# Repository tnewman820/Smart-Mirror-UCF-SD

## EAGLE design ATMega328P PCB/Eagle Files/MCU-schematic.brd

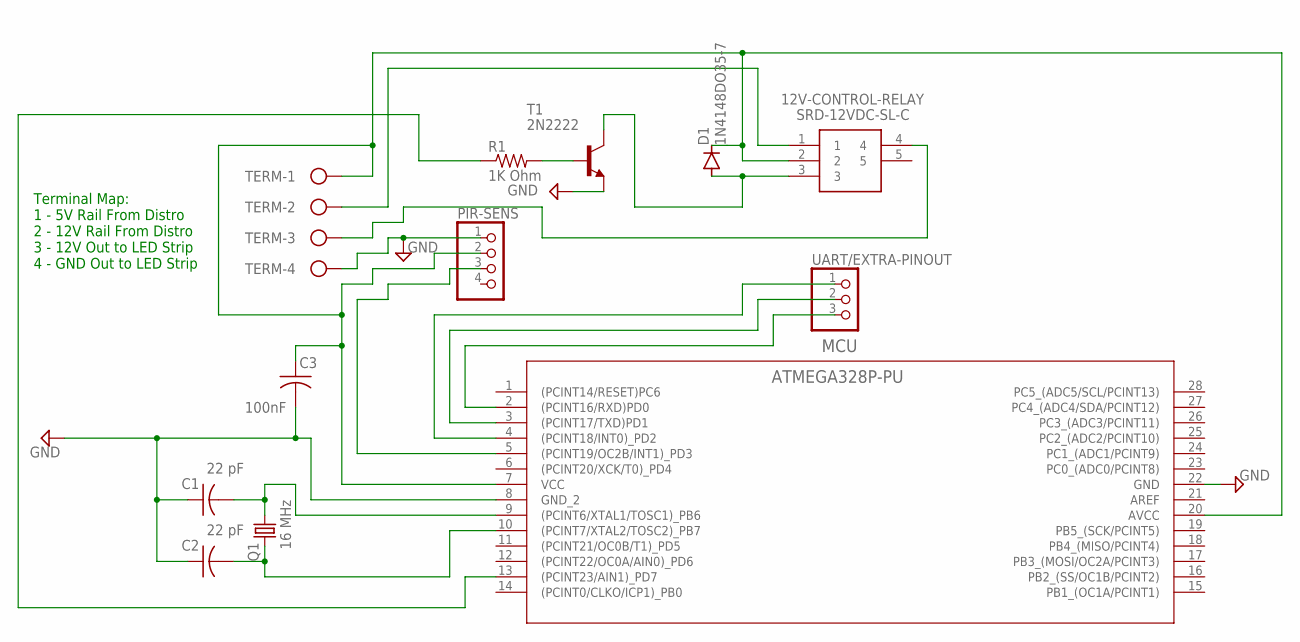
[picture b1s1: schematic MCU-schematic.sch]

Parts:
12V-CONTROL-RELAY: SRD-12VDC-SL-C; SRD
C1, C2: 22 pF; C0805; MPN CL21C220JBANNNC
C3: 100nF; C0805; MPN C0805C104J5RACTU
D1: 1N4148DO35-7; DO35-7
MCU: ATMEGA328P-PU; 28P3_ATM; MPN ATMEGA328P-PU
PIR-SENS: PINHD-1X4; 1X04
Q1: 16 MHz; HC49/S
R1: 1K Ohm; R0805; MPN MPZ2012S102JTD25
T1: 2N2222; TO18; MPN 2N2222
TERM: W237-4
UART/EXTRA-PINOUT: PINHD-1X3; 1X03

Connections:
GND: C1.1, C2.1, C3.2, MCU.8 (GND_2), MCU.22 (GND), PIR-SENS.1, T1.1 (E), TERM.4
unnamed: 12V-CONTROL-RELAY.4, TERM.3
unnamed: C1.2, MCU.9 ((PCINT6/XTAL1/TOSC1)_PB6), Q1.2
unnamed: C2.2, MCU.10 ((PCINT7/XTAL2/TOSC2)_PB7), Q1.1
unnamed: MCU.13 ((PCINT23/AIN1)_PD7), R1.1
unnamed: MCU.2 ((PCINT16/RXD)PD0), UART/EXTRA-PINOUT.3
unnamed: 12V-CONTROL-RELAY.1, TERM.2
unnamed: 12V-CONTROL-RELAY.2, C3.1, D1.C, MCU.7 (VCC), MCU.20 (AVCC), PIR-SENS.2, TERM.1
unnamed: MCU.5 ((PCINT19/OC2B/INT1)_PD3), PIR-SENS.3
unnamed: MCU.3 ((PCINT17/TXD)PD1), UART/EXTRA-PINOUT.2
unnamed: MCU.4 ((PCINT18/INT0)_PD2), UART/EXTRA-PINOUT.1
unnamed: 12V-CONTROL-RELAY.3, D1.A, T1.3 (C)
unnamed: R1.2, T1.2 (B)

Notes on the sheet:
Terminal Map: 1 - 5V Rail From Distro 2 - 12V Rail From Distro 3 - 12V Out to LED Strip 4 - GND Out to LED Strip

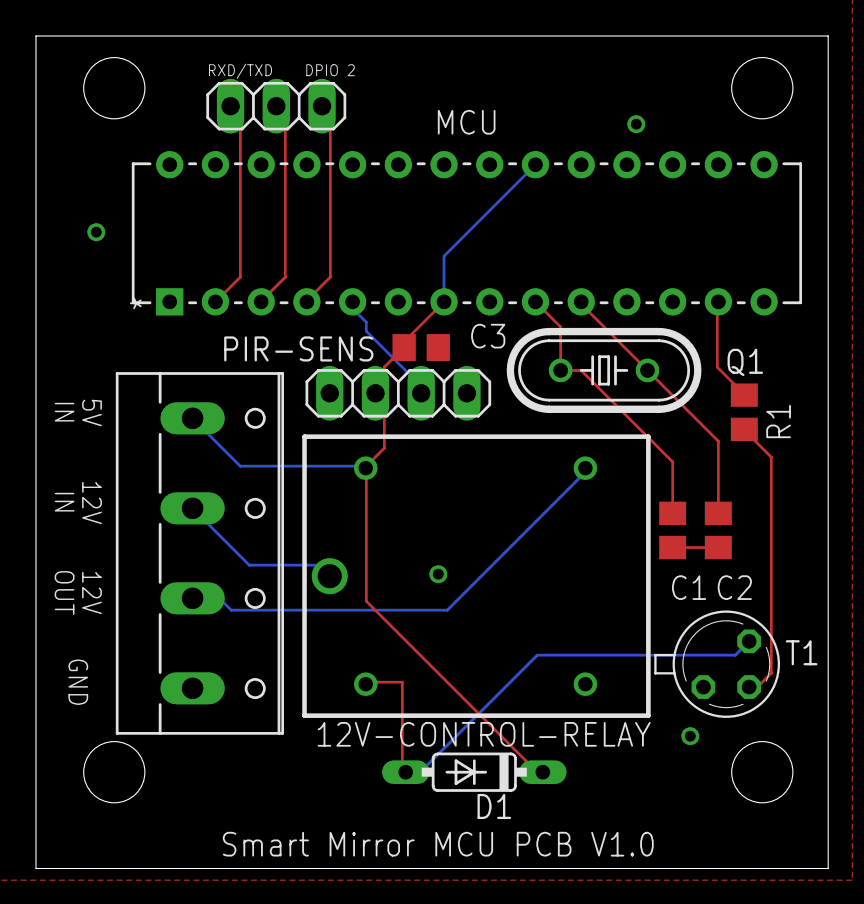
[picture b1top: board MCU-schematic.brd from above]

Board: 2 copper layers, 44.0 x 46.2 mm, 12 parts (0 on the bottom side), 13 nets.

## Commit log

2022-03-03 Setup
2022-03-03 Edits

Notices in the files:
parts and their libraries:
COPYRIGHT: Copyright (C) 2021 Ultra Librarian. All rights reserved.
